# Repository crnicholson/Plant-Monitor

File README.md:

# Plant Monitor

 | 
-- | --
<i>Plant Monitor transmitter circuit board.</i> | <i>Web interface login page.</i>

## About

Plant Monitor is a way to view data from a remote humidity sensor on web interface, which then tells you when you need to water your plants plus the air humidity, soil humidity, air temp, and air pressure. These metrics can be combined with AI to predict forest fires. 

## Get Started

Plant Monitor uses Auth0 to securely log into the web interface. No data or passwords is shown to me. 

PCBs:
1. First, order your transmitter PCB and ground PCB from JLCPCB (soon from me).
2. For now, contact me to add a station number and a passcode for the station. At this time, you'll also need to program your WiFi SSID and password to the ground station PCB and the station number to the transmitter PCB.
3. Turn on the transmitter PCB and place it in the soil of a plant you want to monitor. Make sure to not get it wet!
4. Turn on the ground station PCB. This will receive all the data from the transmitter (sensor) and automatically put it on the web.

Web interface:
1. Next, Go to the [web interface](https://plant-monitor-web.vercel.app) and make an account. 
2. Then, add your station number. Remember to add the password of the station when entering the station number. 
3. The data will now be automatically fetched every 5 seconds. 
4. Lastly, interact with the graphs to see your data over time. 

## Need Help?

Do you have any questions? Are the docs incomplete and you want to ask anything? Do you just want to say hi (or how cool my project is!)?

Reach out to me at [charlienicholsonr@gmail.com](mailto:charlienicholsonr@gmail.com).

## Credits

Thanks to Zach Latta for the idea.

## License

Both the software and documentation are under the [GNU GPL v3 license](https://choosealicense.com/licenses/gpl-3.0/). The hardware and the 3D files are under the [CERN Open Hardware Licence Version 2 - Strongly Reciprocal](https://choosealicense.com/licenses/cern-ohl-s-2.0/). The media is under the [CC BY 4.0 DEED](https://creativecommons.org/licenses/by/4.0/).

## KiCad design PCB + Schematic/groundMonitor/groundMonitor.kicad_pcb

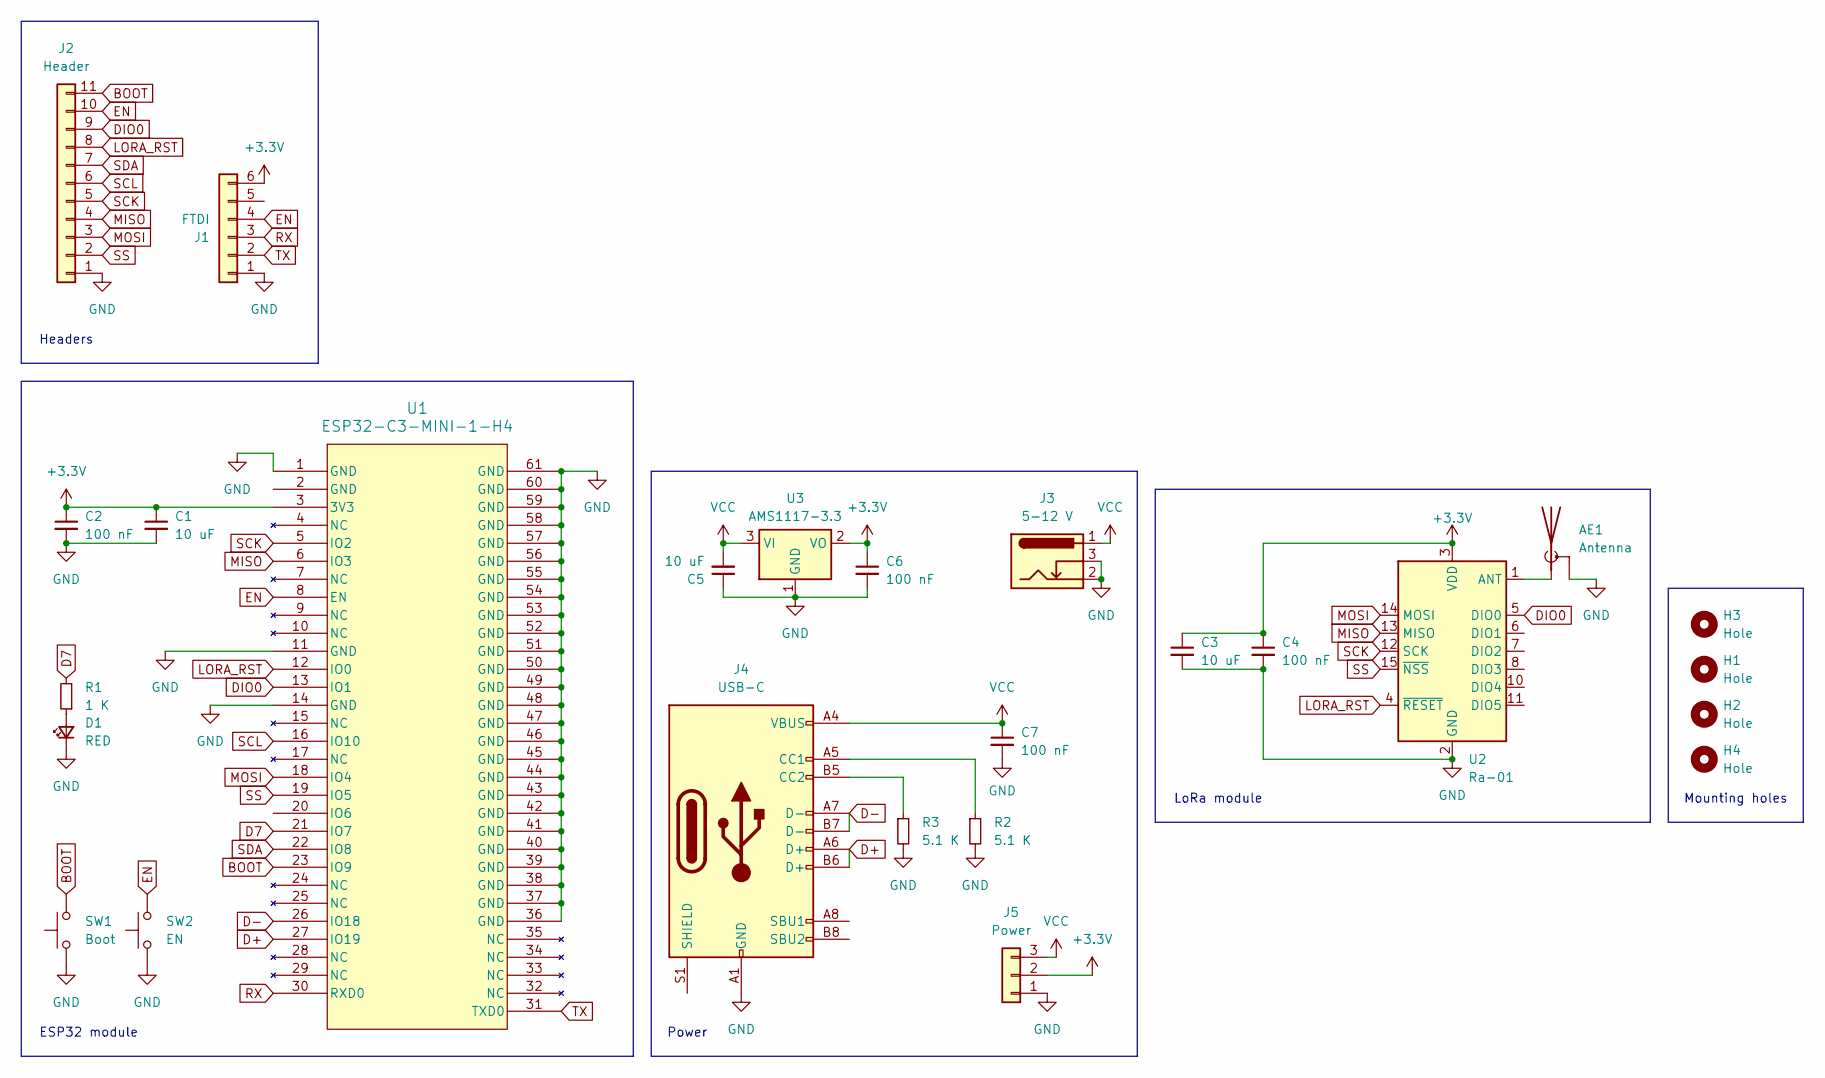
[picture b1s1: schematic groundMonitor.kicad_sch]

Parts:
AE1: Antenna; SMA_Amphenol_132289_EdgeMount
C1, C3, C5: 10 uF; C_0603_1608Metric; LCSC C19702
C2, C4, C6, C7: 100 nF; C_0603_1608Metric; LCSC C14663
D1: RED; LED_0603_1608Metric; LCSC C2286
H1, H2, H3, H4: Hole; MountingHole_3.2mm_M3
J1: FTDI; PinHeader_1x06_P2.54mm_Vertical
J2: Header; PinHeader_1x11_P2.54mm_Vertical
J3: 5-12 V; BarrelJack_Horizontal
J4: USB-C; USB_C_Receptacle_GCT_USB4105-xx-A_16P_TopMnt_Horizontal; LCSC C136423
J5: Power; PinHeader_1x03_P2.54mm_Vertical
R1: 1 K; R_0402_1005Metric; LCSC C11702
R2, R3: 5.1 K; R_0402_1005Metric; LCSC C25905
SW1: Boot; SW_SPST_CK_RS282G05A3; LCSC C2888954
SW2: EN; SW_SPST_CK_RS282G05A3; LCSC C2888954
U1: ESP32-C3-MINI-1-H4; ESP32-C3-MINI-1_EXP; LCSC C2934569
U2: Ra-01; Ai-Thinker-Ra-01-LoRa; LCSC C2830750
U3: AMS1117-3.3; SOT-223-3_TabPin2

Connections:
+3.3V: C1.1, C2.1, C3.1, C4.1, C6.1, J1.6, J5.2, U1.3 (3V3), U2.3 (VDD), U3.2 (VO)
BOOT: J2.11, SW1.2, U1.23 (IO9)
D7: R1.2, U1.21 (IO7)
D+: J4.A6 (D+), J4.B6 (D+), U1.27 (IO19)
D-: J4.A7 (D-), J4.B7 (D-), U1.26 (IO18)
DIO0: J2.9, U1.13 (IO1), U2.5 (DIO0)
EN: J1.4, J2.10, SW2.2, U1.8 (EN)
GND: AE1.2 (Shield), C1.2, C2.2, C3.2, C4.2, C5.1, C6.2, C7.2, D1.1 (K), J1.1, J2.1, J3.2, J3.3, J4.A1 (GND), J4.A12 (GND), J4.B1 (GND), J4.B12 (GND), J5.1, R2.2, R3.2, SW1.1, SW2.1, U1.1 (GND), U1.11 (GND), U1.14 (GND), U1.36 (GND), U1.37 (GND), U1.38 (GND), U1.39 (GND), U1.40 (GND), U1.41 (GND), U1.42 (GND), U1.43 (GND), U1.44 (GND), U1.45 (GND), U1.46 (GND), U1.47 (GND), U1.48 (GND), U1.49 (GND), U1.50 (GND), U1.51 (GND), U1.52 (GND), U1.53 (GND), U1.54 (GND), U1.55 (GND), U1.56 (GND), U1.57 (GND), U1.58 (GND), U1.59 (GND), U1.60 (GND), U1.61 (GND), U2.2 (GND), U2.9 (GND), U2.16 (GND), U3.1 (GND)
LORA_RST: J2.8, U1.12 (IO0), U2.4 (~RESET)
MISO: J2.4, U1.6 (IO3), U2.13 (MISO)
MOSI: J2.3, U1.18 (IO4), U2.14 (MOSI)
unnamed: AE1.1 (A), U2.1 (ANT)
unnamed: D1.2 (A), R1.1
unnamed: J4.A5 (CC1), R2.1
unnamed: J4.B5 (CC2), R3.1
RX: J1.3, U1.30 (RXD0)
SCK: J2.5, U1.5 (IO2), U2.12 (SCK)
SCL: J2.6, U1.16 (IO10)
SDA: J2.7, U1.22 (IO8)
SS: J2.2, U1.19 (IO5), U2.15 (~NSS)
TX: J1.2, U1.31 (TXD0)
VCC: C5.2, C7.1, J3.1, J4.A4 (VBUS), J4.A9 (VBUS), J4.B4 (VBUS), J4.B9 (VBUS), J5.3, U3.3 (VI)

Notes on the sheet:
ESP32 module
Power
Headers
Mounting holes
LoRa module

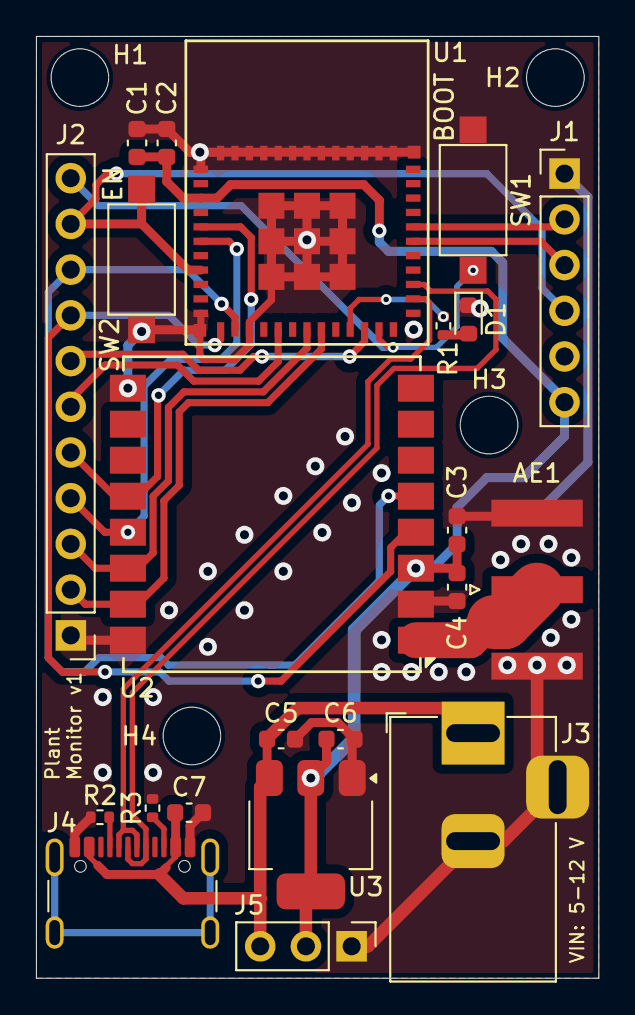
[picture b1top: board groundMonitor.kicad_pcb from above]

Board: 2 copper layers, 31.2 x 52.3 mm, 26 parts (0 on the bottom side), 22 nets.

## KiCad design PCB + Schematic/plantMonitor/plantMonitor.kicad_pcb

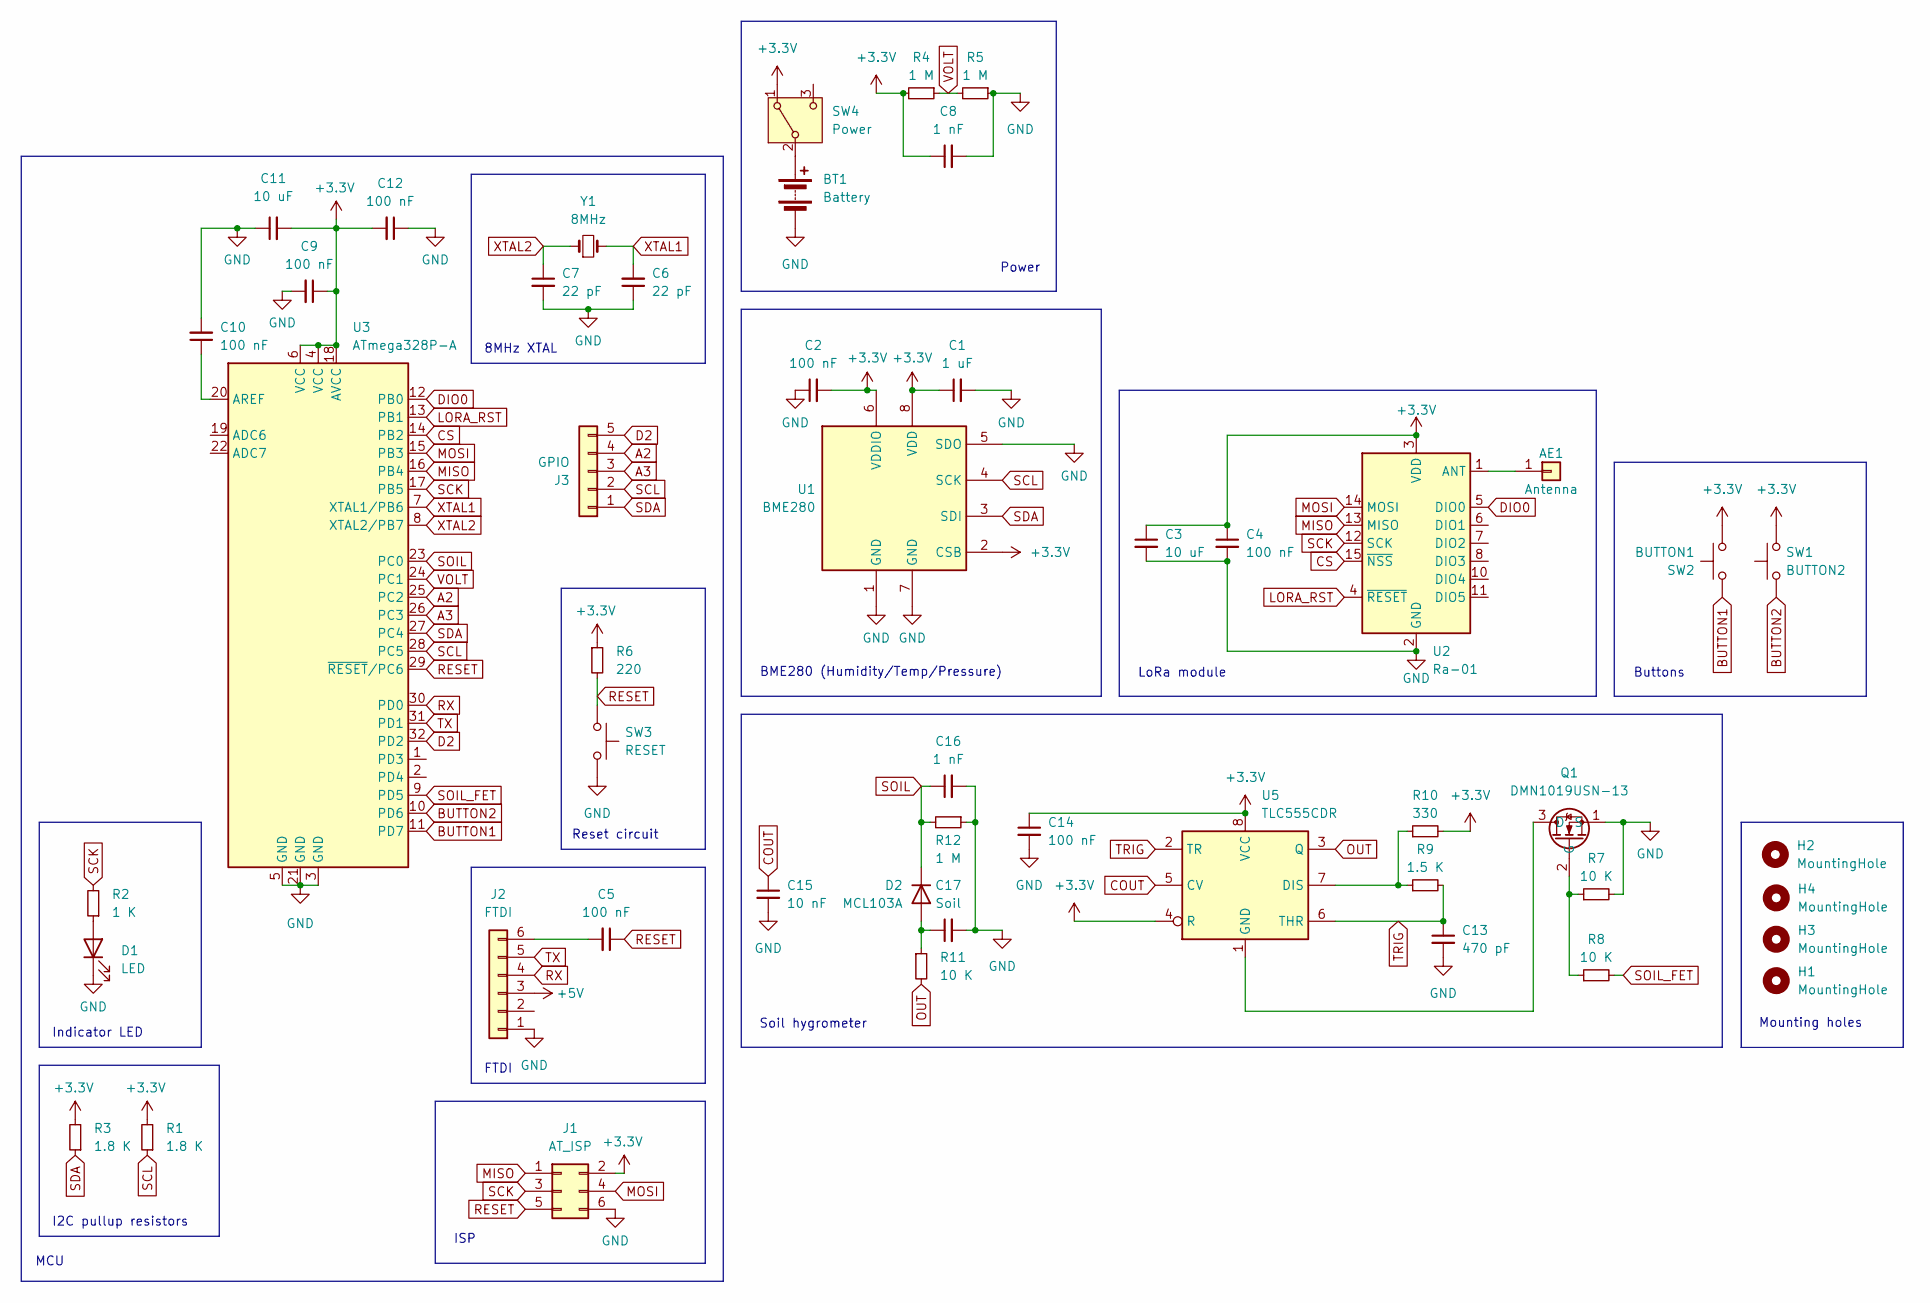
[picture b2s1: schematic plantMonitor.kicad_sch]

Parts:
AE1: Antenna; PinHeader_1x01_P2.54mm_Vertical
BT1: Battery; BatteryHolder_Keystone_2469_2xAAA
C1: 1 uF; C_0402_1005Metric; LCSC C52923
C2, C5, C9, C10, C12, C14: 100 nF; C_0402_1005Metric; LCSC C1525
C3, C11: 10 uF; C_0603_1608Metric; LCSC C19702
C4: 100 nF; C_0603_1608Metric; LCSC C14663
C6, C7: 22 pF; C_0402_1005Metric; LCSC C1555
C8, C16: 1 nF; C_0402_1005Metric; LCSC C1523
C13: 470 pF; C_0603_1608Metric; LCSC C1620
C15: 10 nF; C_0402_1005Metric; LCSC C15195
C17: Soil
D1: LED; LED_0603_1608Metric; LCSC C2286
D2: MCL103A; D_MicroMELF; LCSC C142609
H1, H2, H3, H4: MountingHole; MountingHole_2.2mm_M2
J1: AT_ISP; PinHeader_2x03_P2.54mm_Vertical
J2: FTDI; PinHeader_1x06_P2.54mm_Vertical
J3: GPIO; PinHeader_1x05_P2.54mm_Vertical
Q1: DMN1019USN-13; SC-59_Handsoldering; LCSC C145103
R1, R3: 1.8 K; R_0603_1608Metric; LCSC C4177
R2: 1 K; R_0402_1005Metric; LCSC C11702
R4, R5: 1 M; R_0402_1005Metric; LCSC C26083
R6: 220; R_0402_1005Metric
R7, R11: 10 K; R_0402_1005Metric; LCSC C25744
R8: 10 K; R_0402_1005Metric; LCSC C25077
R9: 1.5 K; R_0402_1005Metric; LCSC C25867
R10: 330; R_0402_1005Metric; LCSC C25104
R12: 1 M; R_0402_1005Metric
SW1: BUTTON2; SW_SPST_CK_RS282G05A3; LCSC C2888954
SW2: BUTTON1; SW_SPST_CK_RS282G05A3; LCSC C2888954
SW3: RESET; SW_SPST_CK_RS282G05A3; LCSC C2888954
SW4: Power; SW_Slide_SPDT
U1: BME280; Bosch_LGA-8_2.5x2.5mm_P0.65mm_ClockwisePinNumbering; LCSC C92489
U2: Ra-01; Ai-Thinker-Ra-01-LoRa; LCSC C2830750
U3: ATmega328P-A; TQFP-32_7x7mm_P0.8mm; LCSC C14877
U5: TLC555CDR; SOIC-8_3.9x4.9mm_P1.27mm; LCSC C6986
Y1: 8MHz; Crystal_HC18-U_Vertical

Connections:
+3.3V: C1.1, C2.2, C3.1, C4.1, C8.1, C9.1, C11.2, C12.2, C14.1, J1.2, R1.2, R3.2, R4.2, R6.1, R10.2, SW1.2, SW2.2, SW4.1 (A), U1.2 (CSB), U1.6 (VDDIO), U1.8 (VDD), U2.3 (VDD), U3.4 (VCC), U3.6 (VCC), U3.18 (AVCC), U5.4 (R), U5.8 (VCC)
+5V: J2.3
A2: J3.4, U3.25 (PC2)
A3: J3.3, U3.26 (PC3)
BUTTON1: SW2.1, U3.11 (PD7)
BUTTON2: SW1.1, U3.10 (PD6)
COUT: C15.1, U5.5 (CV)
CS: U2.15 (~NSS), U3.14 (PB2)
D2: J3.5, U3.32 (PD2)
DIO0: U2.5 (DIO0), U3.12 (PB0)
GND: BT1.2 (-), C1.2, C2.1, C3.2, C4.2, C6.1, C7.2, C8.2, C9.2, C10.2, C11.1, C12.1, C13.2, C14.2, C15.2, C16.2, C17.2, D1.1 (K), J1.6, J2.1, Q1.1 (S), R5.1, R7.2, R12.1, SW3.2, U1.1 (GND), U1.5 (SDO), U1.7 (GND), U2.2 (GND), U2.9 (GND), U2.16 (GND), U3.3 (GND), U3.5 (GND), U3.21 (GND)
LORA_RST: U2.4 (~RESET), U3.13 (PB1)
MISO: J1.1, U2.13 (MISO), U3.16 (PB4)
MOSI: J1.4, U2.14 (MOSI), U3.15 (PB3)
unnamed: AE1.1, U2.1 (ANT)
unnamed: BT1.1 (+), SW4.2 (B)
unnamed: D1.2 (A), R2.1
unnamed: C17.1, D2.2 (A), R11.1
unnamed: C5.2, J2.6
unnamed: Q1.3 (D), U5.1 (GND)
unnamed: Q1.2 (G), R7.1, R8.1
unnamed: C10.1, U3.20 (AREF)
unnamed: R9.1, R10.1, U5.7 (DIS)
OUT: R11.2, U5.3 (Q)
RESET: C5.1, J1.5, R6.2, SW3.1, U3.29 (~RESET/PC6)
RX: J2.4, U3.30 (PD0)
SCK: J1.3, R2.2, U2.12 (SCK), U3.17 (PB5)
SCL: J3.2, R1.1, U1.4 (SCK), U3.28 (PC5)
SDA: J3.1, R3.1, U1.3 (SDI), U3.27 (PC4)
SOIL: C16.1, D2.1 (K), R12.2, U3.23 (PC0)
SOIL_FET: R8.2, U3.9 (PD5)
TRIG: C13.1, R9.2, U5.2 (TR), U5.6 (THR)
TX: J2.5, U3.31 (PD1)
VOLT: R4.1, R5.2, U3.24 (PC1)
XTAL1: C6.2, U3.7 (XTAL1/PB6), Y1.2
XTAL2: C7.1, U3.8 (XTAL2/PB7), Y1.1

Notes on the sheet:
Power
LoRa module
Buttons
Reset circuit
FTDI
Indicator LED
BME280 (Humidity/Temp/Pressure)
I2C pullup resistors
8MHz XTAL
MCU
Soil hygrometer
ISP
Mounting holes

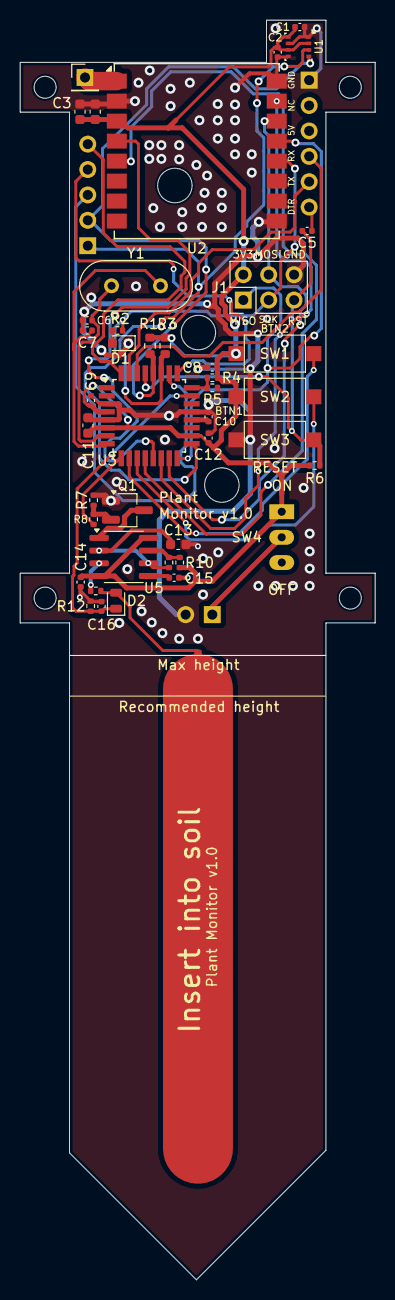
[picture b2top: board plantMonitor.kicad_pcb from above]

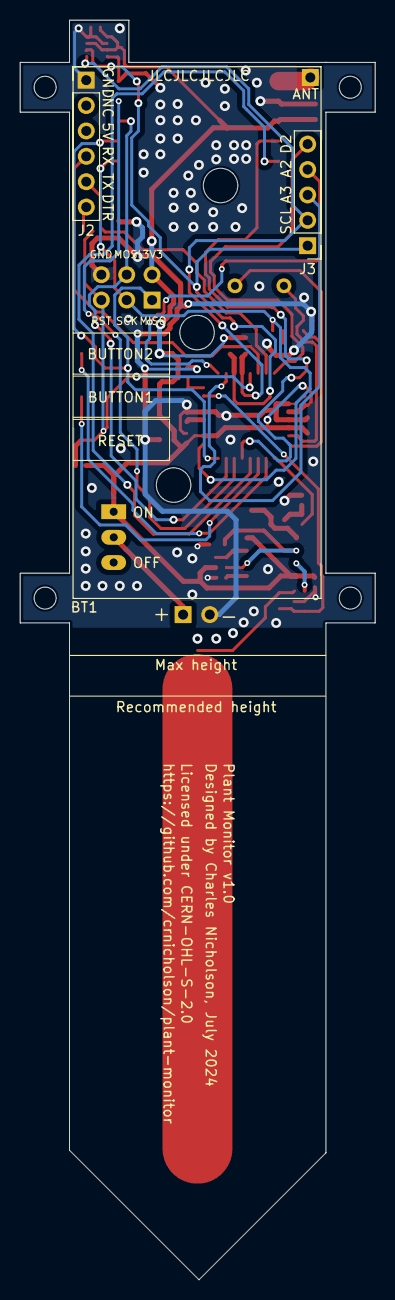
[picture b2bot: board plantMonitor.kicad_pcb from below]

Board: 2 copper layers, 35.5 x 126.0 mm, 50 parts (3 on the bottom side), 35 nets.

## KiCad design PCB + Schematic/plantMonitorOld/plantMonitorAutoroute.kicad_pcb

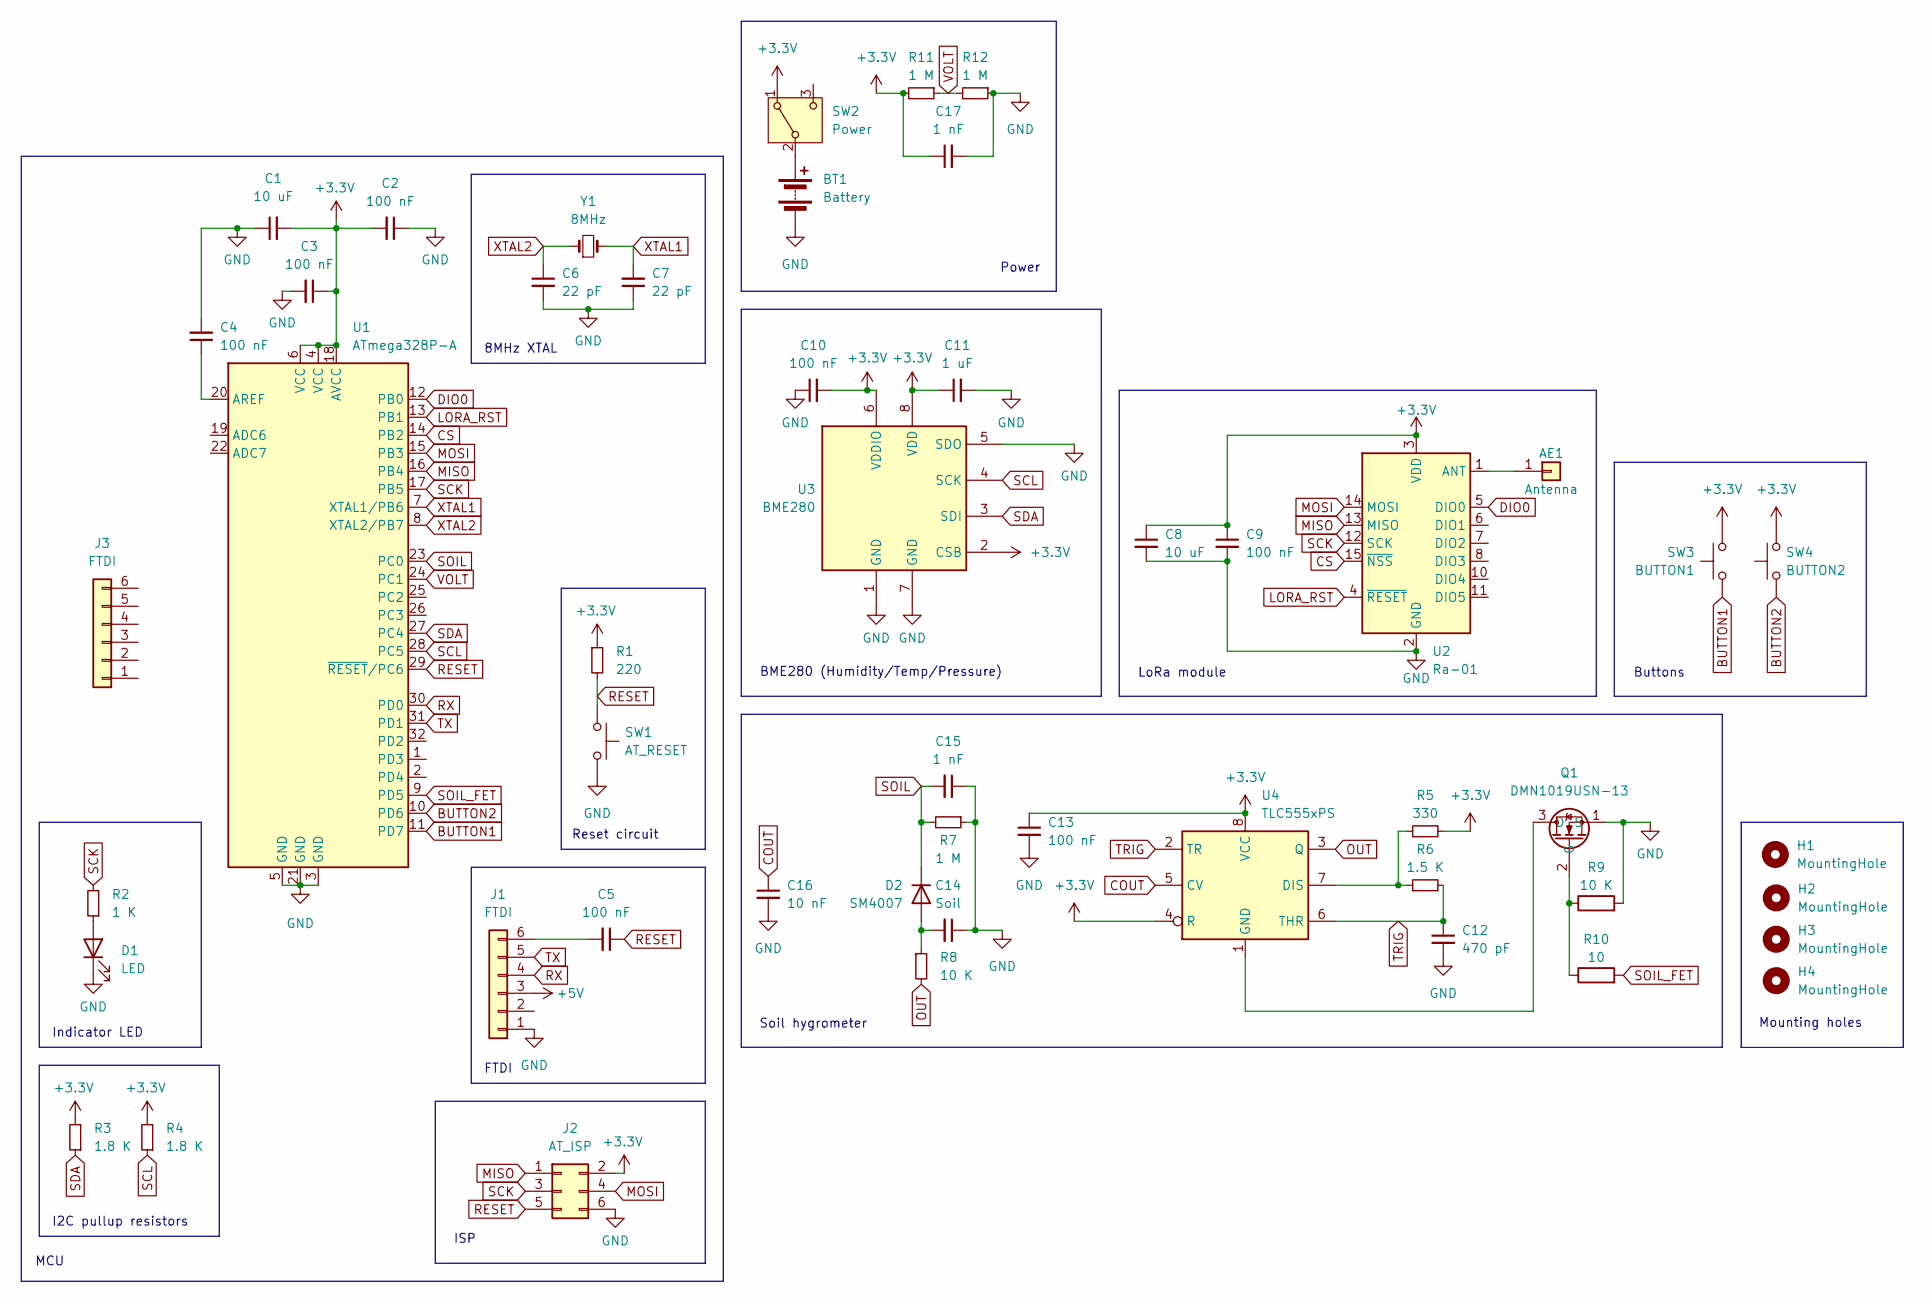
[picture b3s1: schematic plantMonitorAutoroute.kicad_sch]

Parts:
AE1: Antenna; PinHeader_1x01_P2.54mm_Vertical
BT1: Battery; BatteryHolder_Keystone_2469_2xAAA
C1, C8: 10 uF; C_0603_1608Metric; LCSC C19702
C2, C3, C4, C5, C10, C13: 100 nF; C_0402_1005Metric; LCSC C1525
C6, C7: 22 pF; C_0402_1005Metric
C9: 100 nF; C_0603_1608Metric; LCSC C14663
C11: 1 uF; C_0402_1005Metric; LCSC C52923
C12: 470 pF; C_0402_1005Metric
C14: Soil
C15, C17: 1 nF; C_0402_1005Metric
C16: 10 nF; C_0402_1005Metric
D1: LED; LED_0603_1608Metric; LCSC C2286
D2: SM4007; D_MicroMELF
H1, H2, H3, H4: MountingHole; MountingHole_2.2mm_M2
J1, J3: FTDI; PinHeader_1x06_P2.54mm_Vertical
J2: AT_ISP; PinHeader_2x03_P2.54mm_Vertical
Q1: DMN1019USN-13; SC-59_Handsoldering; LCSC C145103
R1: 220; R_0402_1005Metric
R2: 1 K; R_0402_1005Metric; LCSC C11702
R3, R4: 1.8 K; R_0603_1608Metric; LCSC C4177
R5: 330; R_0402_1005Metric
R6: 1.5 K; R_0402_1005Metric
R7, R11, R12: 1 M; R_0402_1005Metric
R8: 10 K; R_0402_1005Metric
R9: 10 K; R_0402_1005Metric; LCSC C25744
R10: 10; R_0402_1005Metric; LCSC C25077
SW1: AT_RESET; SW_SPST_CK_RS282G05A3
SW2: Power; SW_Slide_SPDT
SW3: BUTTON1; SW_SPST_CK_RS282G05A3
SW4: BUTTON2; SW_SPST_CK_RS282G05A3
U1: ATmega328P-A; TQFP-32_7x7mm_P0.8mm
U2: Ra-01; Ai-Thinker-Ra-01-LoRa; LCSC C2830750
U3: BME280; Bosch_LGA-8_2.5x2.5mm_P0.65mm_ClockwisePinNumbering; LCSC C92489
U4: TLC555xPS; VSSOP-8_3.0x3.0mm_P0.65mm
Y1: 8MHz; Crystal_HC18-U_Vertical

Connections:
+3.3V: C1.2, C2.2, C3.1, C8.1, C9.1, C10.2, C11.1, C13.1, C17.1, J2.2, R1.1, R3.2, R4.2, R5.2, R11.2, SW2.1 (A), SW3.2, SW4.2, U1.4 (VCC), U1.6 (VCC), U1.18 (AVCC), U2.3 (VDD), U3.2 (CSB), U3.6 (VDDIO), U3.8 (VDD), U4.4 (R), U4.8 (VCC)
+5V: J1.3
BUTTON1: SW3.1, U1.11 (PD7)
BUTTON2: SW4.1, U1.10 (PD6)
COUT: C16.1, U4.5 (CV)
CS: U1.14 (PB2), U2.15 (~NSS)
DIO0: U1.12 (PB0), U2.5 (DIO0)
GND: BT1.2 (-), C1.1, C2.1, C3.2, C4.2, C6.2, C7.1, C8.2, C9.2, C10.1, C11.2, C12.2, C13.2, C14.1, C15.1, C16.2, C17.2, D1.1 (K), J1.1, J2.6, Q1.1 (S), R7.1, R9.2, R12.1, SW1.2, U1.3 (GND), U1.5 (GND), U1.21 (GND), U2.2 (GND), U2.9 (GND), U2.16 (GND), U3.1 (GND), U3.5 (SDO), U3.7 (GND)
LORA_RST: U1.13 (PB1), U2.4 (~RESET)
MISO: J2.1, U1.16 (PB4), U2.13 (MISO)
MOSI: J2.4, U1.15 (PB3), U2.14 (MOSI)
unnamed: AE1.1, U2.1 (ANT)
unnamed: BT1.1 (+), SW2.2 (B)
unnamed: D1.2 (A), R2.1
unnamed: C14.2, D2.2 (A), R8.1
unnamed: C5.2, J1.6
unnamed: Q1.3 (D), U4.1 (GND)
unnamed: Q1.2 (G), R9.1, R10.1
unnamed: C4.1, U1.20 (AREF)
unnamed: R5.1, R6.1, U4.7 (DIS)
OUT: R8.2, U4.3 (Q)
RESET: C5.1, J2.5, R1.2, SW1.1, U1.29 (~RESET/PC6)
RX: J1.4, U1.30 (PD0)
SCK: J2.3, R2.2, U1.17 (PB5), U2.12 (SCK)
SCL: R4.1, U1.28 (PC5), U3.4 (SCK)
SDA: R3.1, U1.27 (PC4), U3.3 (SDI)
SOIL: C15.2, D2.1 (K), R7.2, U1.23 (PC0)
SOIL_FET: R10.2, U1.9 (PD5)
TRIG: C12.1, R6.2, U4.2 (TR), U4.6 (THR)
TX: J1.5, U1.31 (PD1)
VOLT: R11.1, R12.2, U1.24 (PC1)
XTAL1: C7.2, U1.7 (XTAL1/PB6), Y1.2
XTAL2: C6.1, U1.8 (XTAL2/PB7), Y1.1

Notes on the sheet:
Power
LoRa module
Buttons
Reset circuit
FTDI
Indicator LED
BME280 (Humidity/Temp/Pressure)
I2C pullup resistors
8MHz XTAL
MCU
Soil hygrometer
ISP
Mounting holes

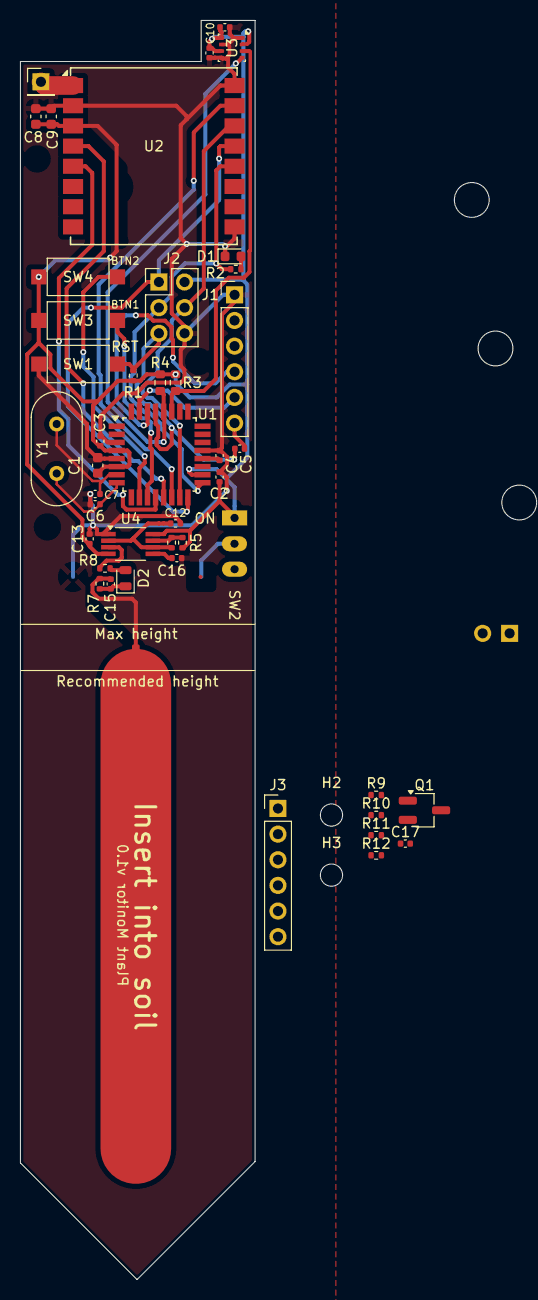
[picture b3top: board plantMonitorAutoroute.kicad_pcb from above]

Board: 2 copper layers, 23.2 x 124.7 mm, 48 parts (1 on the bottom side), 32 nets.

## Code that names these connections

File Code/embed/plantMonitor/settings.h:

/*
settings.h, part of Plant Monitor, to monitor plant water levels.
Copyright (C) 2024 Charles Nicholson

This program is free software: you can redistribute it and/or modify
it under the terms of the GNU General Public License as published by
the Free Software Foundation, either version 3 of the License, or
(at your option) any later version.

This program is distributed in the hope that it will be useful,
but WITHOUT ANY WARRANTY; without even the implied warranty of
MERCHANTABILITY or FITNESS FOR A PARTICULAR PURPOSE.  See the
GNU General Public License for more details.

You should have received a copy of the GNU General Public License
along with this program.  If not, see <https://www.gnu.org/licenses/>.
*/

// Enables
#define DEVMODE         // Enable and disable the serial output.
#define USE_BME         // Enable and disable the BME280.
#define FAST_LORA       // Enable and disable fast LoRa communication, disregarding other LoRa values.
#define CHANGE_TX_POWER // Enable and disable changing the transmit power based on the RSSI.

// Pins.
#define LED 13           // Onboard LED.
#define CS 10            // Chip select for the LoRa module.
#define LORA_RESET 9     // Reset pin of the LoRa module.
#define DIO0 8           // DIO0 pin of the LoRa module.
#define BUTTON1 7        // Extra button for user config.
#define BUTTON2 6        // Extra button for user config.
#define SOIL_FET 5       // FET to turn on the soil sensor.
#define WATER_PIN A0     // Analog pin to read the water level.
#define VOLTMETER_PIN A1 // Analog pin to read the voltage of the battery.

// LoRa, following factors tuned for range.
#define FREQUENCY 915E6     // Frequency of the LoRa module. 433E6 needs a ham radio license in the US.
#define SYNC_WORD 0x40      // Sync word, or password for the communication.
#define SPREADING_FACTOR 10 // Spreading factor of the LoRa communication. Learn more here: https://forum.arduino.cc/t/what-are-the-best-settings-for-a-lora-radio/449528.
#define BANDWIDTH 62.5E3    // Bandwidth of the LoRa.
#define PACKET_FREQUENCY 30 // How many packets of data per hour?

#define DEVICE_ID 1234   // ID of the device, used to identify the device. Do not change this value.
#define DEVICE_PASS 1234 // Do not change this value.

#define GET_RSSI_RATE 1440 // Minutes between getting RSSI checks to lower and raise the power consumption.

// Dynamically change the transmit power based on the RSSI.
#define RSSI_THRESHOLD_HIGH -70 // Strong signal. Getting over this will lower the TX power.
#define RSSI_THRESHOLD_LOW -90  // Weak signal. Getting over this will raise the TX power.

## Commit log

2024-07-27 More PCB
2024-07-31 Intial commit
2024-08-01 stuff
2024-08-01 stupid JS
2024-08-01 I got it mostly working!
2024-08-02 Login and such
2024-08-02 Sign in, font
2024-08-02 JSON, UI
2024-08-02 More UI
2024-08-02 You can download a CSV now!
2024-08-03 Made a landing page + experimenting with other stuff!
2024-08-04 Started making the dashboard page
2024-08-05 Home page, error messages
2024-08-05 CSV!
2024-08-06 Final commit?
2024-08-07 PCB!
2024-08-08 PCB routing
2024-08-09 Silkscreen done
2024-08-09 Part finding
2024-08-09 PCB stuff, file org
2024-08-12 Testing
2024-08-31 Edit README

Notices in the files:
PCB + Schematic/groundMonitor/groundMonitor.kicad_pcb:
Licensed under CERN-OHL-S-2.0
